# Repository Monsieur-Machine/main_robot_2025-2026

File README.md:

# Main Robot 2025-2026

## Description
Main robot code, pcbs and 3d modeling for the Eurobot 2025-2026 competition.

## LICENSES
- This project is open-source : you can redistribute and/or modify it under the term of the **GNU GPLv3**.
  Copyright (C) 2025 Riombotique. See [LICENSE](LICENSE) or [gnu.org/licenses/gpl-3.0.html](https://www.gnu.org/licenses/gpl-3.0.html).

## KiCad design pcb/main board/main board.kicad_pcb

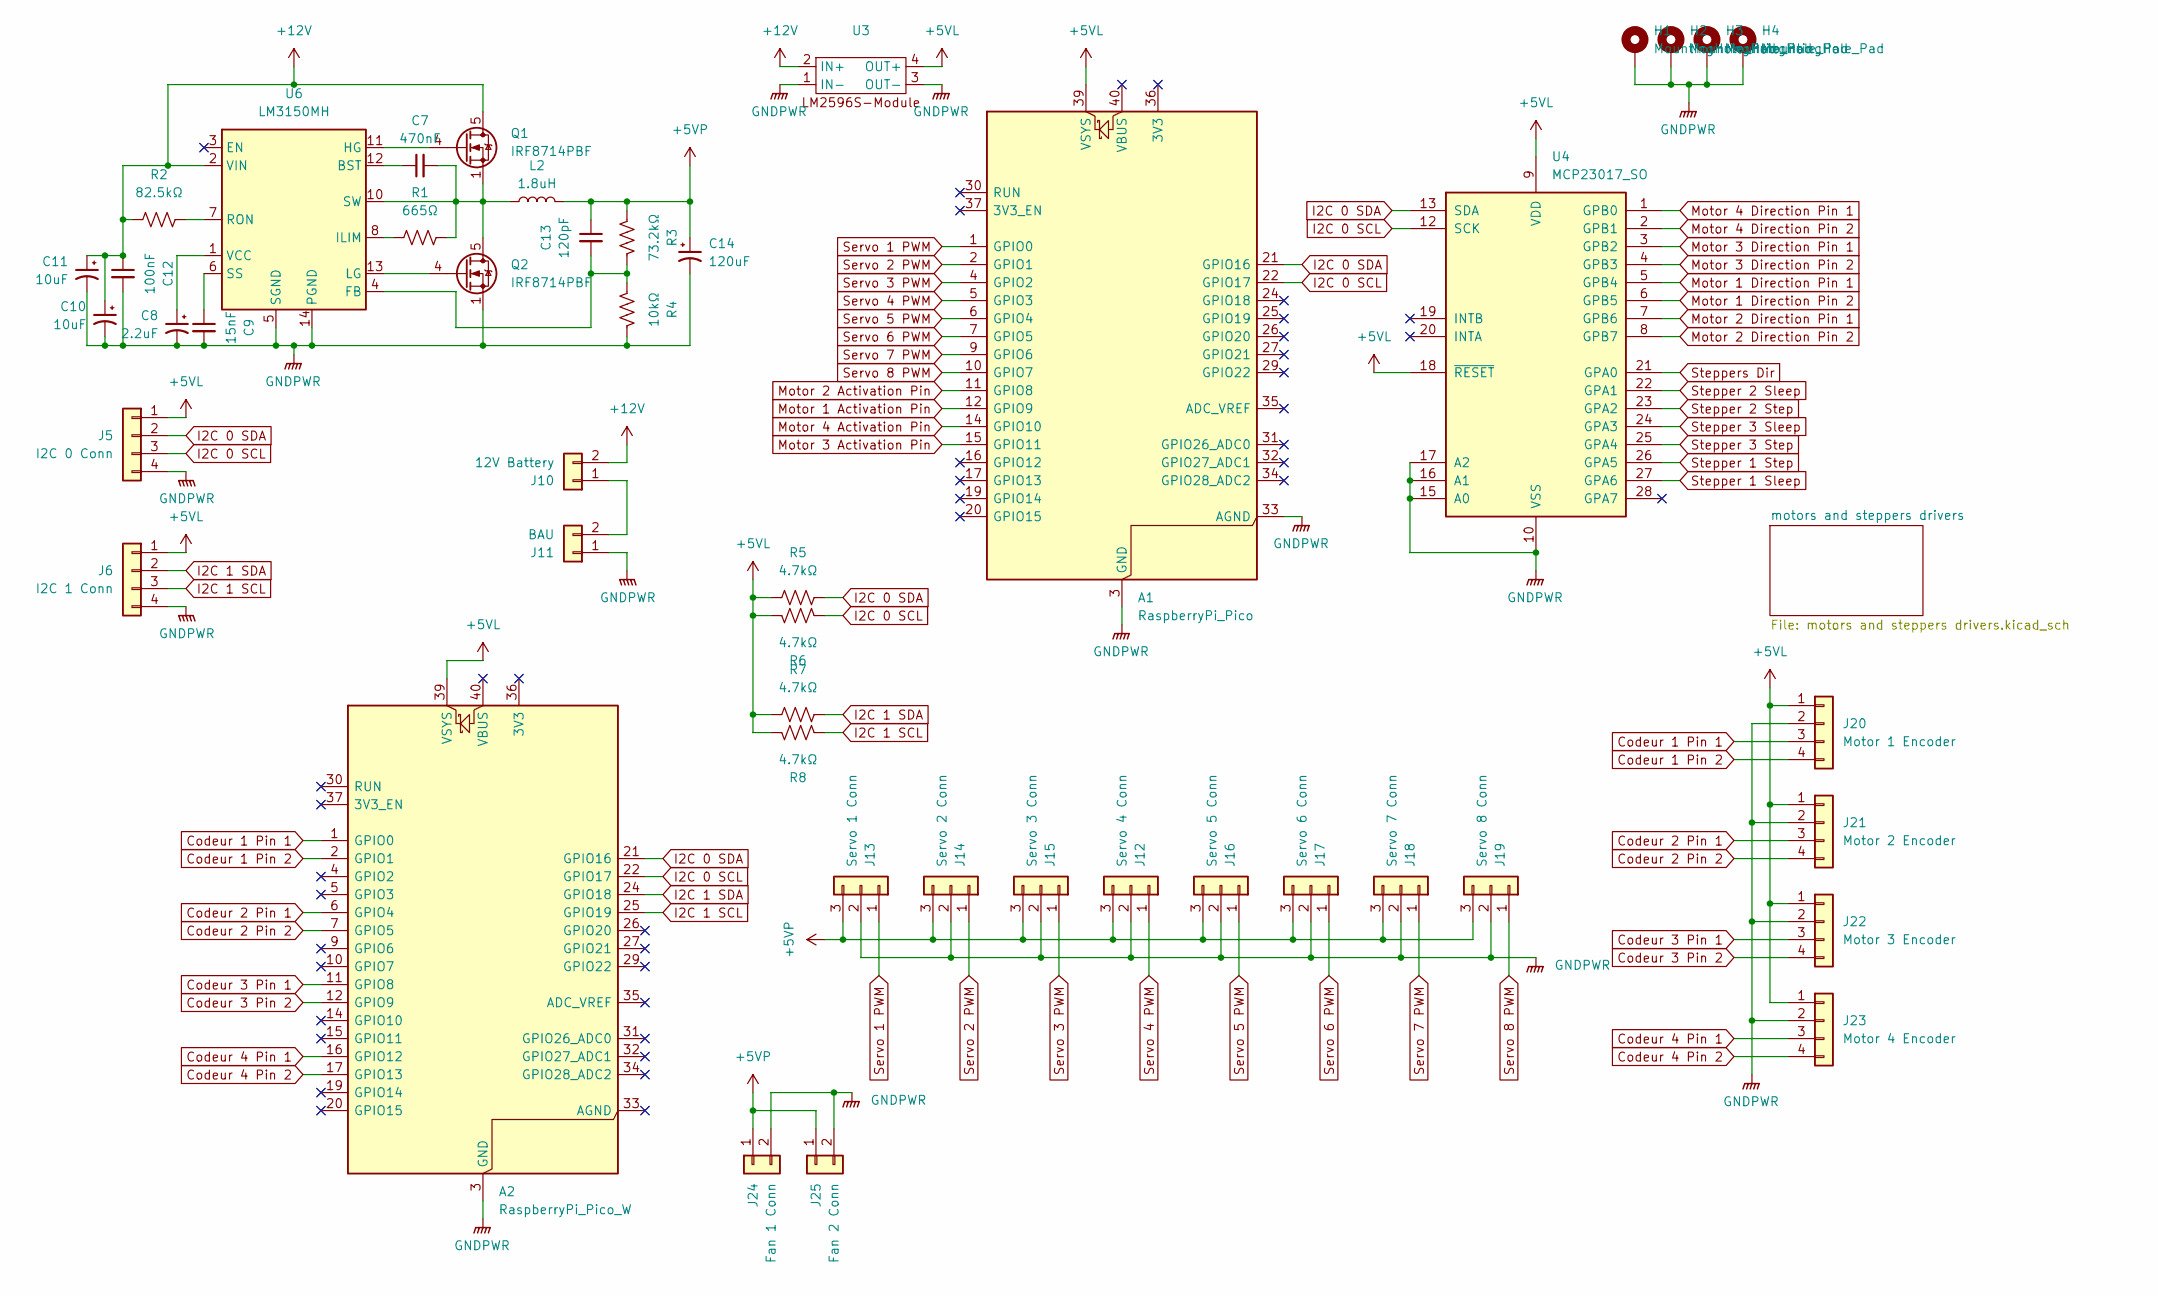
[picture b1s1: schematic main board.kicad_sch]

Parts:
A1: RaspberryPi_Pico; RaspberryPi_Pico_Common_THT
A2: RaspberryPi_Pico_W; RaspberryPi_Pico_Common_THT
C7: 470nF; C_Disc_D4.3mm_W1.9mm_P5.00mm
C8: 2.2uF; CP_Radial_D5.0mm_P2.00mm
C9: 15nF; C_Disc_D3.8mm_W2.6mm_P2.50mm
C10, C11: 10uF; CP_Radial_D6.3mm_P2.50mm
C12: 100nF; C_Disc_D3.8mm_W2.6mm_P2.50mm
C13: 120pF; C_Disc_D4.3mm_W1.9mm_P5.00mm
C14: 120uF; CP_Radial_D6.3mm_P2.50mm
H1, H2, H3, H4: MountingHole_Pad; MountingHole_4mm_Pad
J5: I2C 0 Conn; Molex_KK-254_AE-6410-04A_1x04_P2.54mm_Vertical
J6: I2C 1 Conn; Molex_KK-254_AE-6410-04A_1x04_P2.54mm_Vertical
J10: 12V Battery; Molex_KK-254_AE-6410-02A_1x02_P2.54mm_Vertical
J11: BAU; Molex_KK-254_AE-6410-02A_1x02_P2.54mm_Vertical
J12: Servo 4 Conn; Molex_KK-254_AE-6410-03A_1x03_P2.54mm_Vertical
J13: Servo 1 Conn; Molex_KK-254_AE-6410-03A_1x03_P2.54mm_Vertical
J14: Servo 2 Conn; Molex_KK-254_AE-6410-03A_1x03_P2.54mm_Vertical
J15: Servo 3 Conn; Molex_KK-254_AE-6410-03A_1x03_P2.54mm_Vertical
J16: Servo 5 Conn; Molex_KK-254_AE-6410-03A_1x03_P2.54mm_Vertical
J17: Servo 6 Conn; Molex_KK-254_AE-6410-03A_1x03_P2.54mm_Vertical
J18: Servo 7 Conn; Molex_KK-254_AE-6410-03A_1x03_P2.54mm_Vertical
J19: Servo 8 Conn; Molex_KK-254_AE-6410-03A_1x03_P2.54mm_Vertical
J20: Motor 1 Encoder; Molex_KK-254_AE-6410-04A_1x04_P2.54mm_Vertical
J21: Motor 2 Encoder; Molex_KK-254_AE-6410-04A_1x04_P2.54mm_Vertical
J22: Motor 3 Encoder; Molex_KK-254_AE-6410-04A_1x04_P2.54mm_Vertical
J23: Motor 4 Encoder; Molex_KK-254_AE-6410-04A_1x04_P2.54mm_Vertical
J24: Fan 1 Conn; Molex_KK-254_AE-6410-02A_1x02_P2.54mm_Vertical
J25: Fan 2 Conn; Molex_KK-254_AE-6410-02A_1x02_P2.54mm_Vertical
L2: 1.8uH; L_APV_APH1040
Q1, Q2: IRF8714PBF; SOIC-8_3.9x4.9mm_P1.27mm
R1: 665Ω; R_Axial_DIN0207_L6.3mm_D2.5mm_P10.16mm_Horizontal
R2: 82.5kΩ; R_Axial_DIN0207_L6.3mm_D2.5mm_P10.16mm_Horizontal
R3: 73.2kΩ; R_Axial_DIN0207_L6.3mm_D2.5mm_P10.16mm_Horizontal
R4: 10kΩ; R_Axial_DIN0207_L6.3mm_D2.5mm_P10.16mm_Horizontal
R5, R6, R7, R8: 4.7kΩ; R_Axial_DIN0207_L6.3mm_D2.5mm_P10.16mm_Horizontal
U3: LM2596S-Module
U4: MCP23017_SO; SOIC-28W_7.5x17.9mm_P1.27mm
U6: LM3150MH; HTSSOP-14-1EP_4.4x5mm_P0.65mm_EP3.4x5mm_Mask3x3.1mm

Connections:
+5VL: A1.39 (VSYS), A2.39 (VSYS), J5.1, J6.1, J20.1, J21.1, J22.1, J23.1, R5.1, R6.1, R7.1, R8.1, U3.4 (OUT+), U4.9 (VDD), U4.18 (~RESET); also elsewhere on the board
+5VP: C13.1, C14.1, J12.3, J13.3, J14.3, J15.3, J16.3, J17.3, J18.3, J19.3, J24.1, J25.1, L2.2, R3.2
+12V: C10.1, C11.1, C12.1, J10.2, Q1.5 (D), Q1.6 (D), Q1.7 (D), Q1.8 (D), R2.1, U3.2 (IN+), U6.2 (VIN); also elsewhere on the board
Codeur 1 Pin 1: A2.1 (GPIO0), J20.3
Codeur 1 Pin 2: A2.2 (GPIO1), J20.4
Codeur 2 Pin 1: A2.6 (GPIO4), J21.3
Codeur 2 Pin 2: A2.7 (GPIO5), J21.4
Codeur 3 Pin 1: A2.11 (GPIO8), J22.3
Codeur 3 Pin 2: A2.12 (GPIO9), J22.4
Codeur 4 Pin 1: A2.16 (GPIO12), J23.3
Codeur 4 Pin 2: A2.17 (GPIO13), J23.4
I2C 0 SCL: A1.22 (GPIO17), A2.22 (GPIO17), J5.3, R6.2, U4.12 (SCK)
I2C 0 SDA: A1.21 (GPIO16), A2.21 (GPIO16), J5.2, R5.2, U4.13 (SDA)
I2C 1 SCL: A2.25 (GPIO19), J6.3, R8.2
I2C 1 SDA: A2.24 (GPIO18), J6.2, R7.2
Motor 1 Activation Pin: A1.12 (GPIO9); also elsewhere on the board
Motor 1 Direction Pin 1: U4.5 (GPB4); also elsewhere on the board
Motor 1 Direction Pin 2: U4.6 (GPB5); also elsewhere on the board
Motor 2 Activation Pin: A1.11 (GPIO8); also elsewhere on the board
Motor 2 Direction Pin 1: U4.7 (GPB6); also elsewhere on the board
Motor 2 Direction Pin 2: U4.8 (GPB7); also elsewhere on the board
Motor 3 Activation Pin: A1.15 (GPIO11); also elsewhere on the board
Motor 3 Direction Pin 1: U4.3 (GPB2); also elsewhere on the board
Motor 3 Direction Pin 2: U4.4 (GPB3); also elsewhere on the board
Motor 4 Activation Pin: A1.14 (GPIO10); also elsewhere on the board
Motor 4 Direction Pin 1: U4.1 (GPB0); also elsewhere on the board
Motor 4 Direction Pin 2: U4.2 (GPB1); also elsewhere on the board
unnamed: J10.1, J11.2
unnamed: Q1.4 (G), U6.11 (HG)
unnamed: Q2.4 (G), U6.13 (LG)
unnamed: C7.1, U6.12 (BST)
unnamed: R1.1, U6.8 (ILIM)
unnamed: R2.2, U6.7 (RON)
unnamed: C9.1, U6.6 (SS)
unnamed: C7.2, L2.1, Q1.1 (S), Q1.2 (S), Q1.3 (S), Q2.5 (D), Q2.6 (D), Q2.7 (D), Q2.8 (D), R1.2, U6.10 (SW)
unnamed: C8.1, U6.1 (VCC)
Servo 1 PWM: A1.1 (GPIO0), J13.1
Servo 2 PWM: A1.2 (GPIO1), J14.1
Servo 3 PWM: A1.4 (GPIO2), J15.1
Servo 4 PWM: A1.5 (GPIO3), J12.1
Servo 5 PWM: A1.6 (GPIO4), J16.1
Servo 6 PWM: A1.7 (GPIO5), J17.1
Servo 7 PWM: A1.9 (GPIO6), J18.1
Servo 8 PWM: A1.10 (GPIO7), J19.1
Stepper 1 Sleep: U4.27 (GPA6); also elsewhere on the board
Stepper 1 Step: U4.26 (GPA5); also elsewhere on the board
Stepper 2 Sleep: U4.22 (GPA1); also elsewhere on the board
Stepper 2 Step: U4.23 (GPA2); also elsewhere on the board
Stepper 3 Sleep: U4.24 (GPA3); also elsewhere on the board
Stepper 3 Step: U4.25 (GPA4); also elsewhere on the board
Steppers Dir: U4.21 (GPA0); also elsewhere on the board

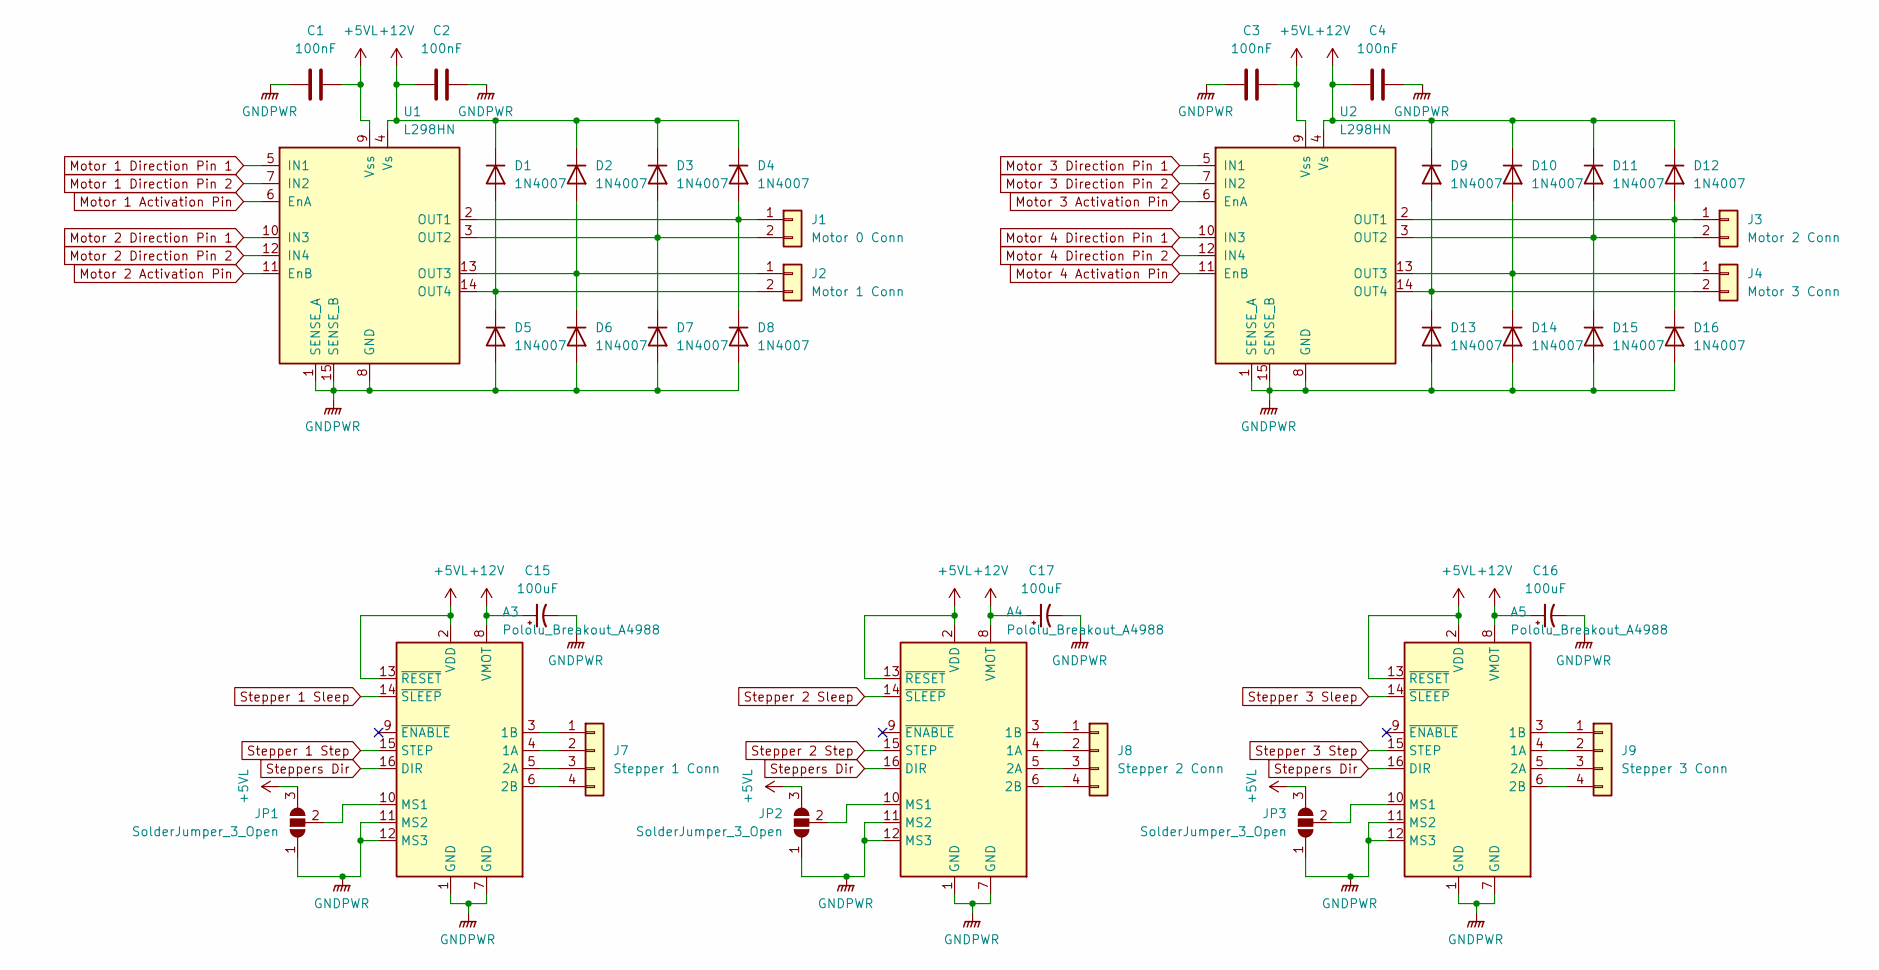
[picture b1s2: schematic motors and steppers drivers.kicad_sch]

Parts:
A3, A4, A5: Pololu_Breakout_A4988; Pololu_Breakout-16_15.2x20.3mm
C1, C2, C3, C4: 100nF; C_Disc_D4.3mm_W1.9mm_P5.00mm
C15, C16, C17: 100uF; CP_Radial_D6.3mm_P2.50mm
D1, D2, D3, D4, D5, D6, D7, D8, D9, D10, D11, D12, D13, D14, D15, D16: 1N4007; D_DO-41_SOD81_P10.16mm_Horizontal
J1: Motor 0 Conn; Molex_KK-254_AE-6410-02A_1x02_P2.54mm_Vertical
J2: Motor 1 Conn; Molex_KK-254_AE-6410-02A_1x02_P2.54mm_Vertical
J3: Motor 2 Conn; Molex_KK-254_AE-6410-02A_1x02_P2.54mm_Vertical
J4: Motor 3 Conn; Molex_KK-254_AE-6410-02A_1x02_P2.54mm_Vertical
J7: Stepper 1 Conn; Molex_KK-254_AE-6410-04A_1x04_P2.54mm_Vertical
J8: Stepper 2 Conn; Molex_KK-254_AE-6410-04A_1x04_P2.54mm_Vertical
J9: Stepper 3 Conn; Molex_KK-254_AE-6410-04A_1x04_P2.54mm_Vertical
JP1, JP2, JP3: SolderJumper_3_Open; SolderJumper-3_P1.3mm_Open_RoundedPad1.0x1.5mm
U1, U2: L298HN; TO-220-15_P2.54x5.08mm_StaggerOdd_Lead4.58mm_Vertical

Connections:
+5VL: A3.2 (VDD), A3.13 (~RESET), A4.2 (VDD), A4.13 (~RESET), A5.2 (VDD), A5.13 (~RESET), C1.1, C3.2, JP1.3 (B), JP2.3 (B), JP3.3 (B), U1.9 (Vss), U2.9 (Vss); also elsewhere on the board
+12V: A3.8 (VMOT), A4.8 (VMOT), A5.8 (VMOT), C2.2, C4.1, C15.1, C16.1, C17.1, D1.1 (K), D2.1 (K), D3.1 (K), D4.1 (K), D9.1 (K), D10.1 (K), D11.1 (K), D12.1 (K), U1.4 (Vs), U2.4 (Vs); also elsewhere on the board
Motor 1 Activation Pin: U1.6 (EnA); also elsewhere on the board
Motor 1 Direction Pin 1: U1.5 (IN1); also elsewhere on the board
Motor 1 Direction Pin 2: U1.7 (IN2); also elsewhere on the board
Motor 2 Activation Pin: U1.11 (EnB); also elsewhere on the board
Motor 2 Direction Pin 1: U1.10 (IN3); also elsewhere on the board
Motor 2 Direction Pin 2: U1.12 (IN4); also elsewhere on the board
Motor 3 Activation Pin: U2.6 (EnA); also elsewhere on the board
Motor 3 Direction Pin 1: U2.5 (IN1); also elsewhere on the board
Motor 3 Direction Pin 2: U2.7 (IN2); also elsewhere on the board
Motor 4 Activation Pin: U2.11 (EnB); also elsewhere on the board
Motor 4 Direction Pin 1: U2.10 (IN3); also elsewhere on the board
Motor 4 Direction Pin 2: U2.12 (IN4); also elsewhere on the board
unnamed: A3.4 (1A), J7.2
unnamed: A3.3 (1B), J7.1
unnamed: A3.5 (2A), J7.3
unnamed: A3.6 (2B), J7.4
unnamed: A3.10 (MS1), JP1.2 (C)
unnamed: A4.4 (1A), J8.2
unnamed: A4.3 (1B), J8.1
unnamed: A4.5 (2A), J8.3
unnamed: A4.6 (2B), J8.4
unnamed: A4.10 (MS1), JP2.2 (C)
unnamed: A5.4 (1A), J9.2
unnamed: A5.3 (1B), J9.1
unnamed: A5.5 (2A), J9.3
unnamed: A5.6 (2B), J9.4
unnamed: A5.10 (MS1), JP3.2 (C)
unnamed: D1.2 (A), D5.1 (K), J2.2, U1.14 (OUT4)
unnamed: D2.2 (A), D6.1 (K), J2.1, U1.13 (OUT3)
unnamed: D3.2 (A), D7.1 (K), J1.2, U1.3 (OUT2)
unnamed: D4.2 (A), D8.1 (K), J1.1, U1.2 (OUT1)
unnamed: D10.2 (A), D14.1 (K), J4.1, U2.13 (OUT3)
unnamed: D11.2 (A), D15.1 (K), J3.2, U2.3 (OUT2)
unnamed: D12.2 (A), D16.1 (K), J3.1, U2.2 (OUT1)
unnamed: D9.2 (A), D13.1 (K), J4.2, U2.14 (OUT4)
Stepper 1 Sleep: A3.14 (~SLEEP); also elsewhere on the board
Stepper 1 Step: A3.15 (STEP); also elsewhere on the board
Stepper 2 Sleep: A4.14 (~SLEEP); also elsewhere on the board
Stepper 2 Step: A4.15 (STEP); also elsewhere on the board
Stepper 3 Sleep: A5.14 (~SLEEP); also elsewhere on the board
Stepper 3 Step: A5.15 (STEP); also elsewhere on the board
Steppers Dir: A3.16 (DIR), A4.16 (DIR), A5.16 (DIR); also elsewhere on the board

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
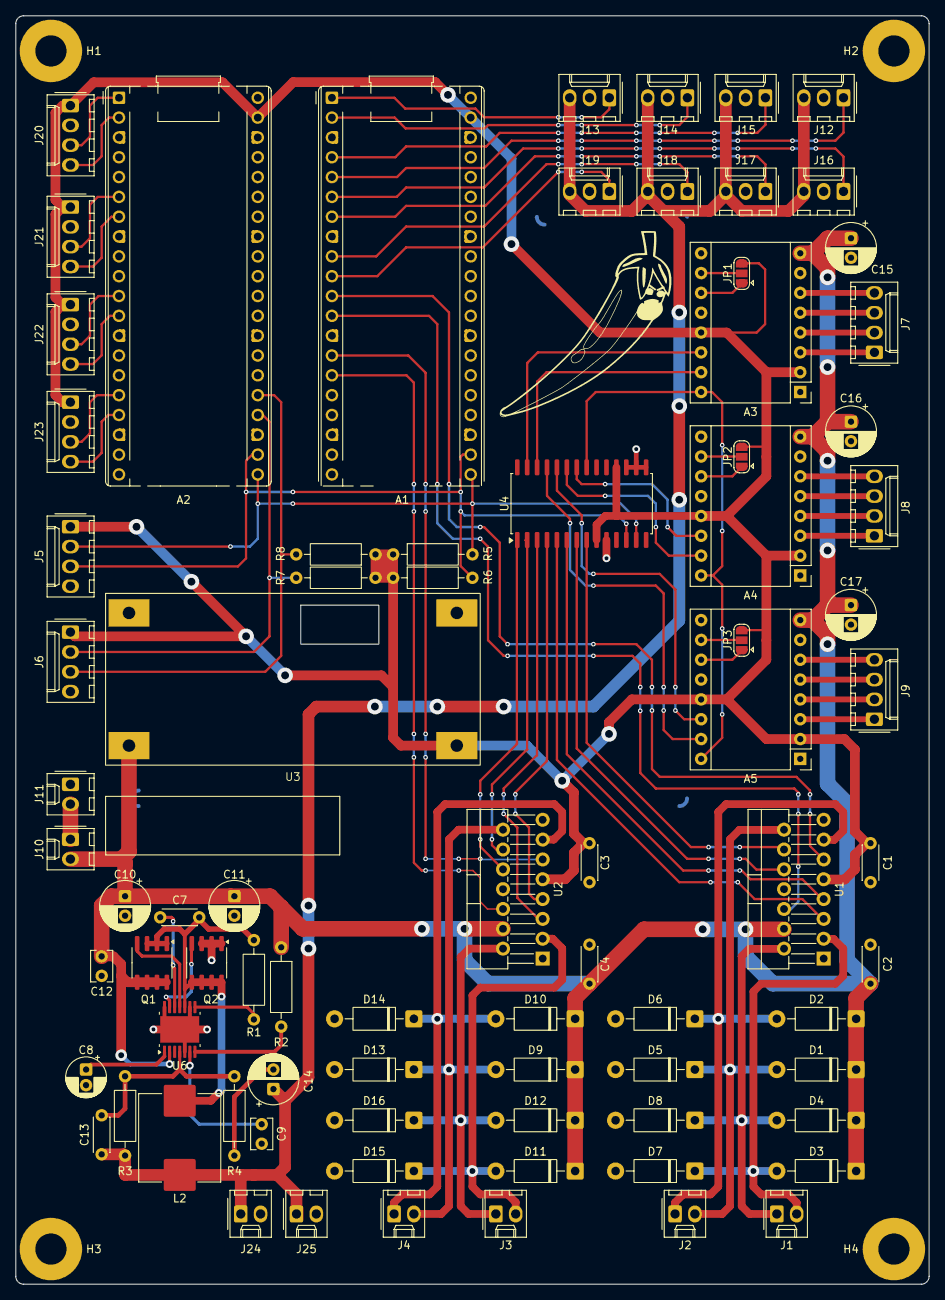
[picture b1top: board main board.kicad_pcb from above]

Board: 2 copper layers, 117.0 x 162.5 mm, 84 parts (0 on the bottom side), 76 nets.

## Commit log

2025-10-01 Starting new pcb and copying code from last year main robot
2025-10-01 Added license and removed PCB folder
2025-10-01 Added pico 3D model and started main pcb
2025-10-01 Started to implement L298N DC Motors drivers
2025-10-02 Finished motor driver on main pcb
2025-10-02 Added logical 5v regulator schematic
2025-10-03 Added MCP23017 gpio extender to the motor driver and found a 8A 5v regulator. Neither of them are connected correctly
2025-10-03 Almost finished implementation of 5v power regulator
2025-10-03 Finished 5V power alimentation and mcp23017 connection
2025-10-03 Started to implement steppers motors drivers
2025-10-03 Finished to implement and connect every 3 steppers drivers
2025-10-04 Theroricaly finished main board !
2025-10-04 Reformated scheatic size and expoted in pdf
2025-10-12 Modified LM2596S to be a module.
2025-10-12 Changed some capacitors and assigned every component.
2025-10-13 Started Motors Wiring
2025-10-13 Finished DC motors wiring aand started 5VP regulator.
2025-10-14 Finished DC motors wiring and started 5VP regulator.
2025-10-14 Rearanged board
2025-10-14 Finished wiring 5VP, created mass plane and started to wire motor drivers.
2025-10-15 Continued Conecting motors drivers
2025-10-15 Almost finished wiring motors drivers and continued connecting the rest. Also modified the LM2596S Module to put a hole in the board
2025-10-15 Updated PDF schematic
2025-10-15 Replaced L298Ns footprints to a vertical version and almost finished rewiring them...
2025-10-16 Changed largeur of pistes and finished rewiring DC motors drivers
2025-10-16 Almost finished PCB !
2025-10-17 Finished PCB !
2025-10-17 Added Aisler DRC and corrected errors.
2025-10-19 Added motors encoders connectors
2025-10-20 Changed empreinte and rewired them to match commanded ones
2025-10-20 Moved component info and hided unused texts
2025-10-20 Added logos and aisler logo placeholder
2025-10-20 Actualiser README.md
2025-10-21 Corrected superposition errors
2025-10-26 Added Jumpers To select Steppers speed
2025-10-27 Finished correcting and updating footprints for capacitors and started to change connectors footprints
2025-10-27 Finished adding holes and connectors
2025-11-15 Updated PCB and corrected errors
2025-11-28 Updated PCB
2026-01-11 Staging For Transfer
2026-01-31 Renamed folders
2026-01-31 Updated gitignore
2026-01-31 Corrected WiFi and UDP
2026-01-31 Corrected some typo
2026-01-31 Remove unused file
2026-02-04 Updated pico files and udp communication
2026-02-06 Fixed return state of wifi operator init function
2026-02-09 More clarity
2026-02-09 Lowered I2C bus speed
2026-02-17 Almost working gyro
2026-02-24 Working motion control
2026-02-24 Updated gyro and pico files
2026-02-25 Commit caca
2026-02-25 Fonctionne avec l'USB déconnecté et l'esclave en mode minimal + moteur
2026-02-25 Ajout Motion controleur en mode minimal
2026-02-25 Suppression des 200 ms d'attente côté main controler
2026-02-25 Rétablissement du pilotage par gyroscope
2026-02-25 Correction de la tempo qui n'était pas une tempo + suppresion code commenté
2026-02-26 Réglage asservissement
2026-02-28 Working servos (almost) and cleaned robot.h/.c for both controllers

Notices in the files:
README.md:
License: GPL v3
